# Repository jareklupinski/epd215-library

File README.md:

This is a library for the Pervasive Displays Epaper Screen E2215CS062.
This library has been written for and fully supports the Teensy-LC and the rest of the Teensy 3.x series and uses their native SPI library.
It can also be used with Arduino, ESP8266, and most available microcontrollers, optionally using a slower bitbanged interface.

This code and further updates will be hosted at https://github.com/jareklupinski/epd215-library

These displays use SPI to communicate. For more information on the signaling protocol used, please see the official datasheet for all the details: http://www.pervasivedisplays.com/LiteratureRetrieve.aspx?ID=232068

Written by Jarek Lupinski for Soniktech LLC  
Adapted from Adafruit GFX library driver code
BSD license, check license.txt for more information
All text above must be included in any redistribution

```
I have just stumbled across the OSHPark shared design for ePaper interface and I have ordered the PCBs.
After assembling the interface I could not get this library example files to work.
After many experiments and probing I realized that the newer board with temperature sensor was designed and the two signals for RES# and BUSY (pins 14 and 15) are swapped between the two designs.
Since the older board is referenced in OSHPark and Hackaday, please note the different pin assignments in the example files like bellow:

// initialize epaper with pin numbers for cs, dc, rs, bs, d0, d1 for software SPI
//EPD215 epaper( 17, 16, 15, 14, 13, 11 );
// initialize epaper with pin numbers for cs, dc, rs, bs for hardware SPI
//EPD215 epaper( 17, 16, 15, 14 );
// for original interface board design (minus temp sensor) use these settings (pins 14 and 15 swapped):
// initialize epaper with pin numbers for cs, dc, rs, bs, d0, d1 for software SPI
//EPD215 epaper( 17, 16, 14, 15, 13, 11 );
// initialize epaper with pin numbers for cs, dc, rs, bs for hardware SPI
//EPD215 epaper( 17, 16, 14, 15 );

Thank you,
Michal Sokolowski
```

To download: click the DOWNLOADS button in the top right corner, rename the uncompressed folder EPD215. Check that the EPD215 folder contains EPD215.cpp and EPD215.h

Place the EPD215 library folder in your <arduinosketchfolder>/libraries/ folder. You may need to create the libraries subfolder if its your first library. Restart the IDE.

You will also have to download the Adafruit GFX Graphics core which does all the circles, text, rectangles, etc. You can get it from
https://github.com/adafruit/Adafruit-GFX-Library
and download / install that library as well

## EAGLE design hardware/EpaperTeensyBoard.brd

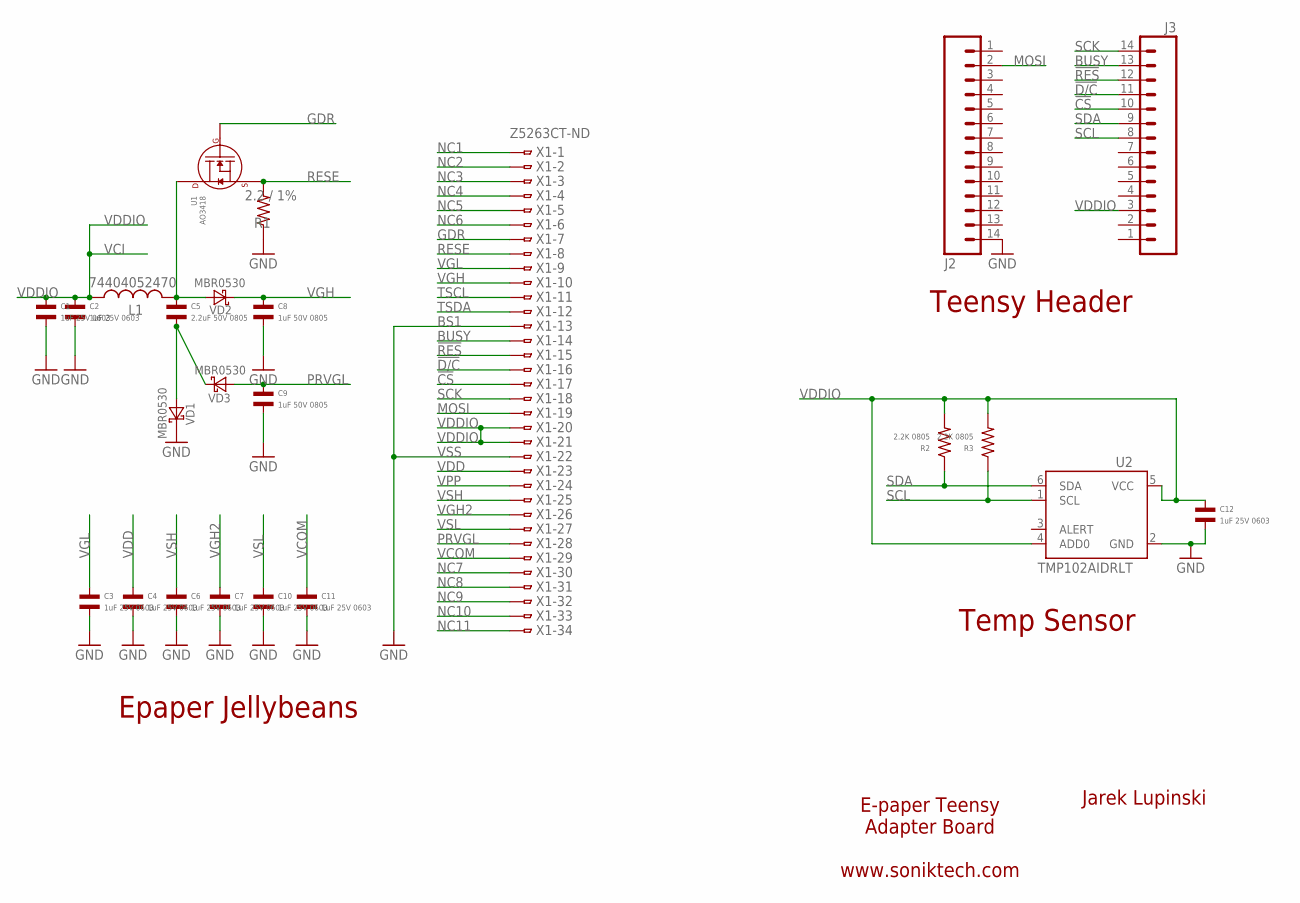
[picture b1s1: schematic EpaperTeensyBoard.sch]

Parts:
C1, C2, C3, C4, C6, C7, C10, C11, C12: 1uF 25V 0603; C0603
C5: 2.2uF 50V 0805; C0805
C8, C9: 1uF 50V 0805; C0805
J2, J3: M14; 1X14
L1: 74404052470; POWER-CHOKE_WE-TPC
R1: 2.2 / 1%; R0805
R2, R3: 2.2K 0805; R0805
U1: AO3418; SOT-23-3
U2: TMP102AIDRLT; SOT563
VD1, VD2, VD3: MBR0530; SOD123
X1: Z5263CT-ND; XF3M-34

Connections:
!CS: J3.10, X1.17
!D/C: J3.11, X1.16
!RES: J3.12, X1.15
BUSY: J3.13, X1.14
GDR: U1.P$1 (GATE), X1.7
GND: C1.P$2, C2.P$2, C3.P$2, C4.P$2, C6.P$2, C7.P$2, C8.P$2, C9.P$2, C10.P$2, C11.P$2, C12.P$2, J2.14, R1.P$1, U2.2 (GND), VD1.C, X1.13, X1.22
MOSI: J2.2, X1.19
unnamed: C5.P$1, L1.2, U1.P$3 (DRAIN), VD2.A
unnamed: C5.P$2, VD1.A, VD3.C
NC1: X1.1
NC2: X1.2
NC3: X1.3
NC4: X1.4
NC5: X1.5
NC6: X1.6
NC7: X1.30
NC8: X1.31
NC9: X1.32
NC10: X1.33
NC11: X1.34
PRVGL: C9.P$1, VD3.A, X1.28
RESE: R1.P$2, U1.P$2 (SOURCE), X1.8
SCK: J3.14, X1.18
SCL: J3.8, R3.P$1, U2.1 (SCL)
SDA: J3.9, R2.P$1, U2.6 (SDA)
TSCL: X1.11
TSDA: X1.12
VCOM: C11.P$1, X1.29
VDD: C4.P$1, X1.23
VDDIO: C1.P$1, C2.P$1, C12.P$1, J3.3, L1.1, R2.P$2, R3.P$2, U2.4 (ADD0), U2.5 (VCC), X1.20, X1.21
VGH: C8.P$1, VD2.C, X1.10
VGH2: C7.P$1, X1.26
VGL: C3.P$1, X1.9
VPP: X1.24
VSH: C6.P$1, X1.25
VSL: C10.P$1, X1.27

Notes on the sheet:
BS1
VSS
VCI
Teensy Header
Temp Sensor
Epaper Jellybeans
Jarek Lupinski
E-paper Teensy Adapter Board www.soniktech.com

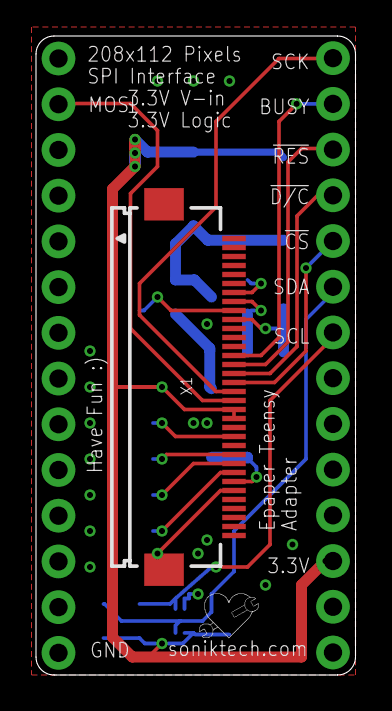
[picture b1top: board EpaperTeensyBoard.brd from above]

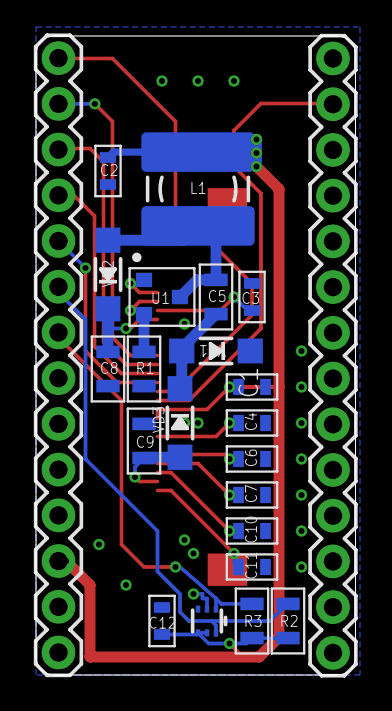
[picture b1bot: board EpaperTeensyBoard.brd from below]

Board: 2 copper layers, 17.8 x 35.5 mm, 24 parts (23 on the bottom side), 22 nets.

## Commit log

2017-02-06 V 1.0 with Examples
    Added files to conform to Arduino Library Specs
2017-02-09 Update EPD215.cpp
    Commented out SPI.beginTransaction( SPISettings( 1000000, MSBFIRST, SPI_MODE0 )); , as it causes issues with Devices that don't have that function, and default SPI transaction settings work well.
2017-02-20 Added Hardware Design Files
2017-02-20 Create assets
2017-02-20 Rename EpaperTeensyBoard.brd to hardware/EpaperTeensyBoard.brd
2017-02-20 Rename EpaperTeensyBoard.sch to hardware/EpaperTeensyBoard.sch
2017-04-07 Get rid of warnings due to useless usage of i in for
2018-07-05 Create LICENSE
2020-12-29 Added rotation, corrected license
2020-12-29 Added rotation, corrected license (#8)

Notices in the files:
parts and their libraries:
SparkFun-Sensors: Licensing: Creative Commons ShareAlike 4.0 International - https://creativecommons.org/licenses/by-sa/4.0
